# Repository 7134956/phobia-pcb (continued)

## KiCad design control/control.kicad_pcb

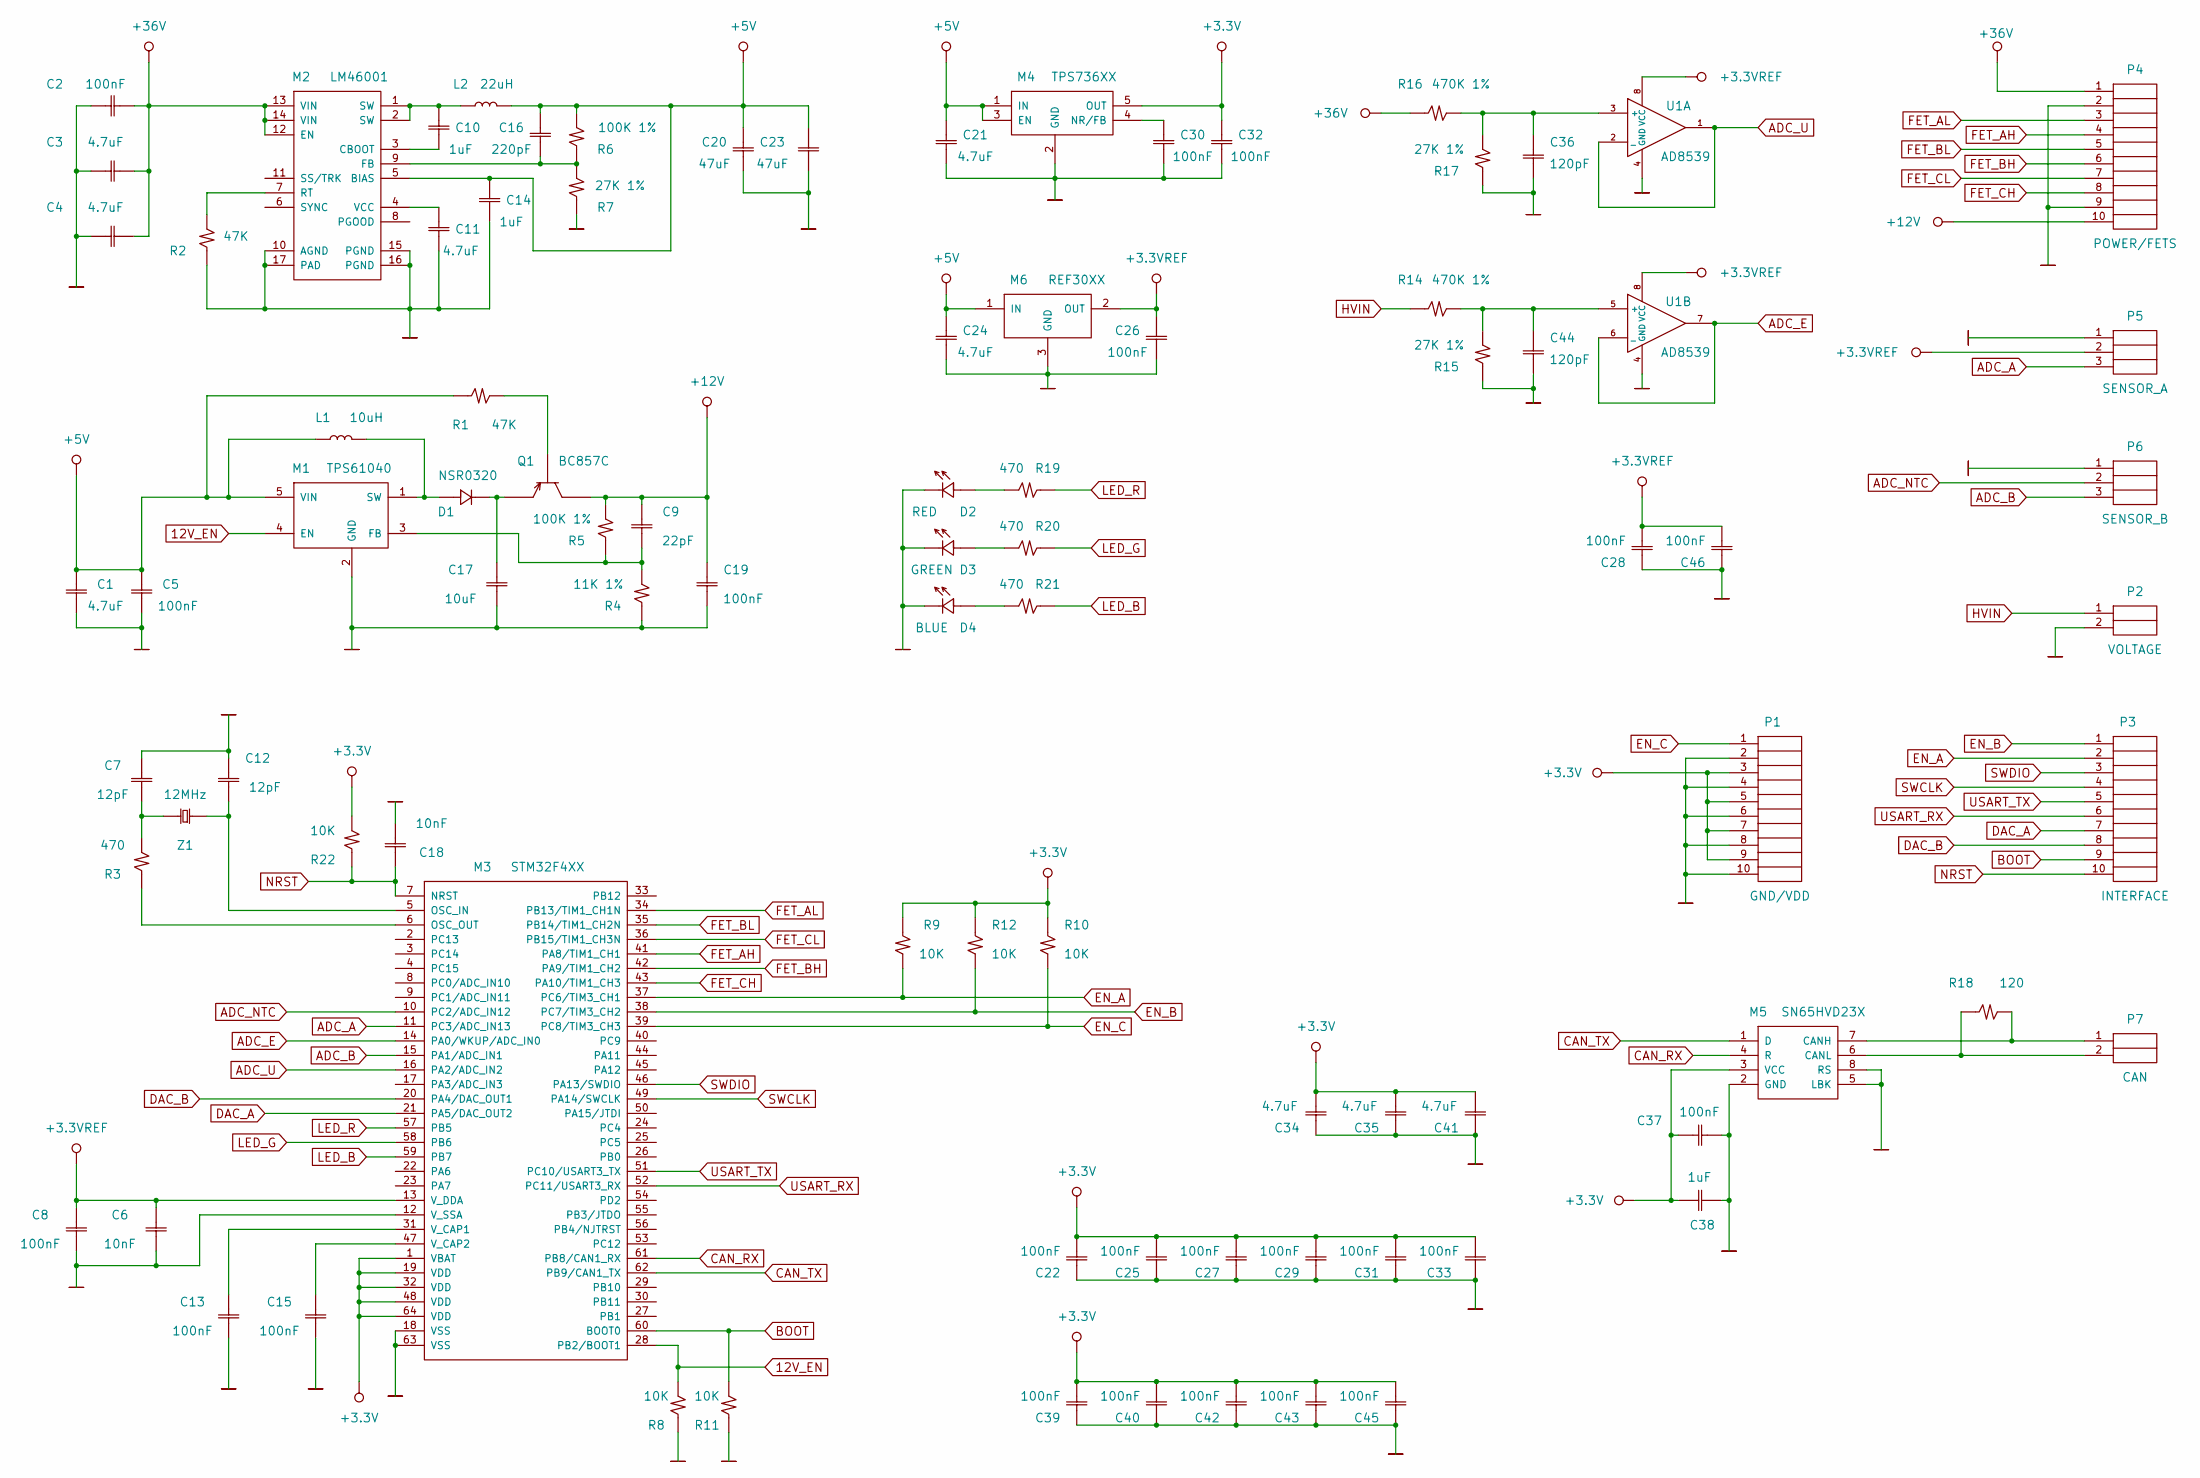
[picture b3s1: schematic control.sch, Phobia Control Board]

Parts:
C1, C11, C21, C24, C34, C35, C41: 4.7uF; SM0805
C2: 100nF; SM0805
C3, C4: 4.7uF; SM2220
C5, C8, C13, C15, C19, C22, C25, C26, C27, C28, C29, C30, C31, C32, C33, C37, C39, C40, C42, C43, C45, C46: 100nF; SM0603
C6, C18: 10nF; SM0603
C7, C12: 12pF; SM0603
C9: 22pF; SM0603
C10, C14, C38: 1uF; SM0805
C16: 220pF; SM0603
C17: 10uF; SM1210
C20, C23: 47uF; SM1210
C36, C44: 120pF; SM0603
D1: NSR0320; SOD-232
D2: RED; SM0603
D3: GREEN; SM0603
D4: BLUE; SM0603
L1: 10uH; COIL3
L2: 22uH; COIL8
M1: TPS61040; SOT23-5
M2: LM46001; HTSSOP16
M3: STM32F4XX; LQFP-64
M4: TPS736XX; SOT23-5
M5: SN65HVD23X; SO8
M6: REF30XX; SOT23
P1: GND/VDD; PLS10
P2: VOLTAGE; PLS2
P3: INTERFACE; PLS10
P4: POWER/FETS; PLS10
P5: SENSOR_A; PLS3
P6: SENSOR_B; PLS3
P7: CAN; PLS2
Q1: BC857C; SOT23
R1, R2: 47K; SM0603
R3, R19, R20, R21: 470; SM0603
R4: 11K 1%; SM0603
R5, R6: 100K 1%; SM0603
R7, R15, R17: 27K 1%; SM0603
R8, R9, R10, R11, R12, R22: 10K; SM0603
R14, R16: 470K 1%; SM0603
R18: 120; SM1206
U1: AD8539; MSOP8
Z1: 12MHz; SMD_Z3225

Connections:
12V_EN: M1.4 (EN), M3.28 (PB2/BOOT1), R8.2
+3.3V: C22.1, C25.1, C27.1, C29.1, C31.1, C32.1, C33.1, C34.1, C35.1, C37.2, C38.2, C39.1, C40.1, C41.1, C42.1, C43.1, C45.1, M3.1 (VBAT), M3.19 (VDD), M3.32 (VDD), M3.48 (VDD), M3.64 (VDD), M4.5 (OUT), M5.3 (VCC), P1.3, P1.5, P1.7, P1.9, R9.1, R10.1, R12.1, R22.2
+3.3VREF: C6.1, C8.1, C26.1, C28.1, C46.1, M3.13 (V_DDA), M6.2 (OUT), P5.2, U1.8 (VCC)
+5V: C1.1, C5.1, C14.1, C16.1, C20.1, C21.1, C23.1, C24.1, L1.1, L2.2, M1.5 (VIN), M2.5 (BIAS), M4.1 (IN), M4.3 (EN), M6.1 (IN), R1.1, R6.2
+12V: C9.1, C19.1, P4.10, Q1.2 (C), R5.2
+36V: C2.1, C3.1, C4.1, M2.12 (EN), M2.13 (VIN), M2.14 (VIN), P4.1, R16.1
ADC_A: M3.11 (PC3/ADC_IN13), P5.3
ADC_B: M3.15 (PA1/ADC_IN1), P6.3
ADC_E: M3.14 (PA0/WKUP/ADC_IN0), U1.6 (_), U1.7
ADC_NTC: M3.10 (PC2/ADC_IN12), P6.2
ADC_U: M3.16 (PA2/ADC_IN2), U1.1, U1.2 (_)
BOOT: M3.60 (BOOT0), P3.9, R11.2
CAN_RX: M3.61 (PB8/CAN1_RX), M5.4 (R)
CAN_TX: M3.62 (PB9/CAN1_TX), M5.1 (D)
DAC_A: M3.21 (PA5/DAC_OUT2), P3.7
DAC_B: M3.20 (PA4/DAC_OUT1), P3.8
EN_A: M3.37 (PC6/TIM3_CH1), P3.2, R9.2
EN_B: M3.38 (PC7/TIM3_CH2), P3.1, R12.2
EN_C: M3.39 (PC8/TIM3_CH3), P1.1, R10.2
FET_AH: M3.41 (PA8/TIM1_CH1), P4.4
FET_AL: M3.34 (PB13/TIM1_CH1N), P4.3
FET_BH: M3.42 (PA9/TIM1_CH2), P4.6
FET_BL: M3.35 (PB14/TIM1_CH2N), P4.5
FET_CH: M3.43 (PA10/TIM1_CH3), P4.8
FET_CL: M3.36 (PB15/TIM1_CH3N), P4.7
GND: C1.2, C2.2, C3.2, C4.2, C5.2, C6.2, C7.1, C8.2, C11.2, C12.1, C13.2, C14.2, C15.2, C17.2, C18.1, C19.2, C20.2, C21.2, C22.2, C23.2, C24.2, C25.2, C26.2, C27.2, C28.2, C29.2, C30.2, C31.2, C32.2, C33.2, C34.2, C35.2, C36.2, C37.1, C38.1, C39.2, C40.2, C41.2, C42.2, C43.2, C44.2, C45.2, C46.2, D2.1, D3.1, D4.1, M1.2 (GND), M2.10 (AGND), M2.15 (PGND), M2.16 (PGND), M2.17 (PAD), M3.12 (V_SSA), M3.18 (VSS), M3.63 (VSS), M4.2 (GND), M5.2 (GND), M5.5 (LBK), M5.8 (RS), M6.3 (GND), P1.2, P1.4, P1.6, P1.8, P1.10, P2.2, P4.2, P4.9, P5.1, P6.1, R2.1, R4.1, R7.1, R8.1, R11.1, R15.1, R17.1, U1.4 (GND)
HVIN: P2.1, R14.1
LED_B: M3.59 (PB7), R21.1
LED_G: M3.58 (PB6), R20.1
LED_R: M3.57 (PB5), R19.1
NRST: C18.2, M3.7 (NRST), P3.10, R22.1
unnamed: C7.2, R3.2, Z1.1
unnamed: C9.2, M1.3 (FB), R4.2, R5.1
unnamed: C10.1, L2.1, M2.1 (SW), M2.2 (SW)
unnamed: C10.2, M2.3 (CBOOT)
unnamed: C11.1, M2.4 (VCC)
unnamed: C12.2, M3.5 (OSC_IN), Z1.2
unnamed: C13.1, M3.31 (V_CAP1)
unnamed: C15.1, M3.47 (V_CAP2)
unnamed: C16.2, M2.9 (FB), R6.1, R7.2
unnamed: C17.1, D1.1, Q1.3 (E)
unnamed: C30.1, M4.4 (NR/FB)
unnamed: C36.1, R16.2, R17.2, U1.3 (+)
unnamed: C44.1, R14.2, R15.2, U1.5 (+)
unnamed: D1.2, L1.2, M1.1 (SW)
unnamed: D2.2, R19.2
unnamed: D3.2, R20.2
unnamed: D4.2, R21.2
unnamed: M2.7 (RT), R2.2
unnamed: M3.6 (OSC_OUT), R3.1
unnamed: M5.6 (CANL), P7.2, R18.1
unnamed: M5.7 (CANH), P7.1, R18.2
unnamed: Q1.1 (B), R1.2
SWCLK: M3.49 (PA14/SWCLK), P3.4
SWDIO: M3.46 (PA13/SWDIO), P3.3
USART_RX: M3.52 (PC11/USART3_RX), P3.6
USART_TX: M3.51 (PC10/USART3_TX), P3.5

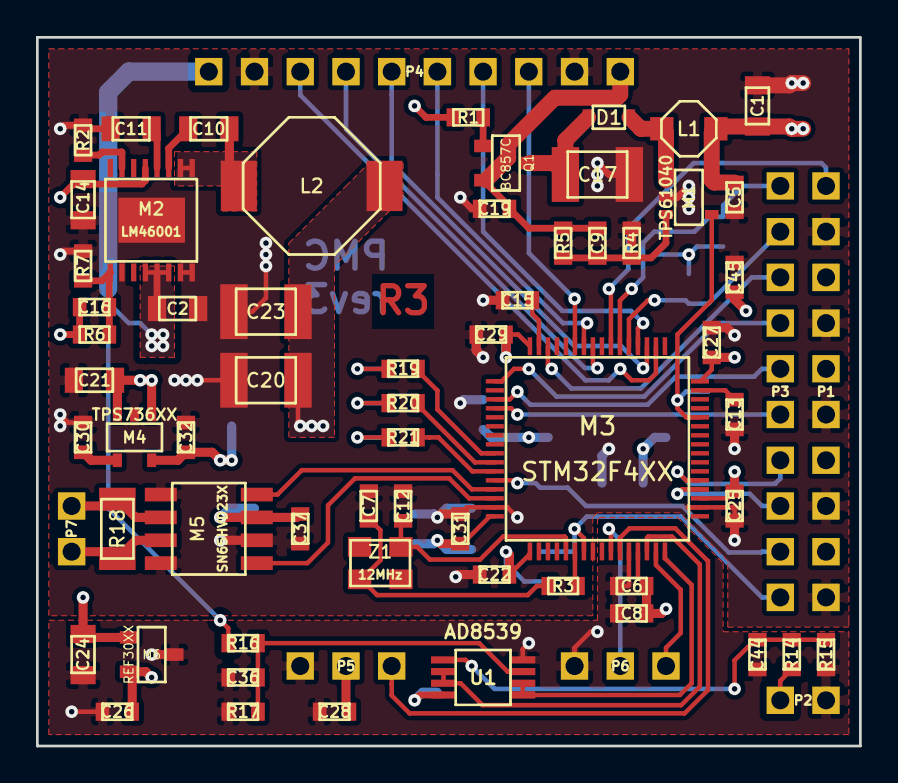
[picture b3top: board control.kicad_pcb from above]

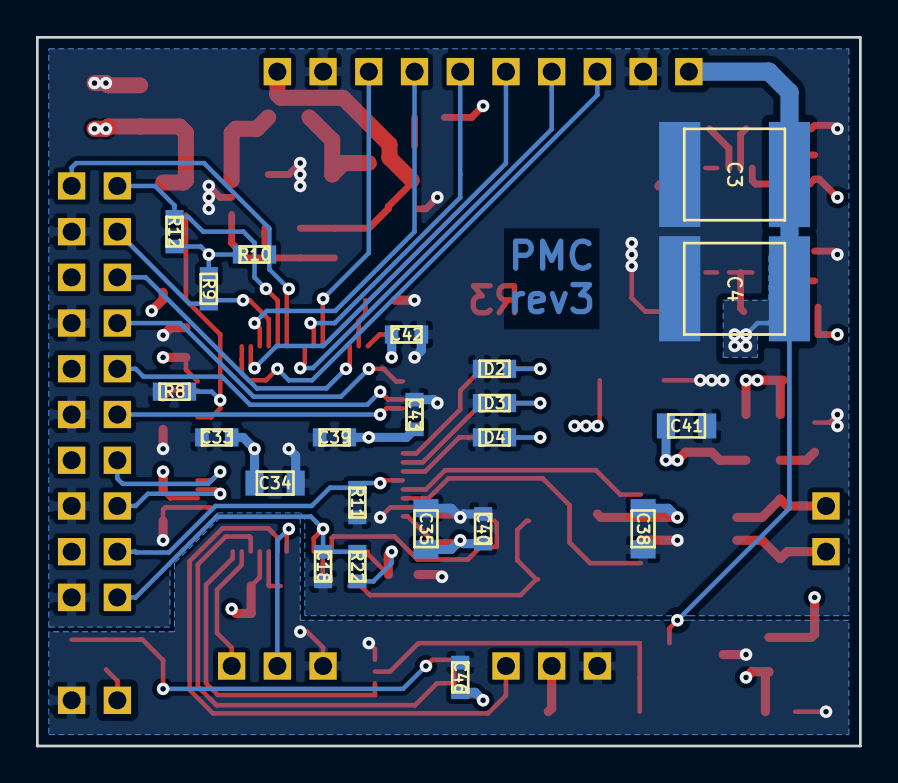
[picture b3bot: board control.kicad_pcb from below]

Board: 4 copper layers, 45.7 x 39.4 mm, 89 parts (22 on the bottom side), 57 nets.

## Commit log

2016-02-01 Initial commit with revision 1 draft.
2016-02-01 Added README.
2016-02-01 Fixed a mistake.
2016-02-02 Added tag rev1 for changeset 2688a04983ae
2016-02-02 Going to make a rev2.
2016-02-06 Small changes, enlarged supply rail clearance.
2016-02-09 Added OpAmp buffer, a lot of small fixes.
2016-02-15 Added encoder inputs on control board, removed SWD, changed USART.
2016-02-16 Added DAC outputs, SWD outputs, fixes.
2016-02-16 Added jumper outputs.
2016-03-25 Accumulated changes, large track width, encoder/hall interface, etc.
2016-03-30 Reduced decoupling capacitor bank like ESC, also added two row of pins, small fixes.
2016-03-31 Renew annotaion of power board, minor fixes.
2016-03-31 Added separate +5v polygon on control board.
2016-09-08 Fixed power pads mask clearance.
2016-09-19 Replaced ACS7XX sensors to the current shunt amplifiers.
2016-09-23 Small fixes for rev2.
2016-09-24 Added tag rev2 for changeset 79f38fd7bc1a
2016-10-30 Fixed a few small mistakes.
2017-05-09 Added revison 3.
2017-05-09 Added tag rev3 for changeset 9c580cb6d94c
2017-07-08 Fixed a little mistake.
2018-01-07 There is a single board design.
2018-04-01 Small fixes in schematic and pcb.
2018-04-06 Minor fixing.
2018-04-12 Fixed SilkS layers.
2018-04-14 Removed large cap outlines from SilkS layers.
2018-04-17 Fixed SilkS layers again.
2018-04-17 Fixed soldermask clearance.
2018-04-26 Added tag rev4a for changeset c6011a8fe1b5
2018-07-29 A new design with two 6-layer pcbs.
2018-08-25 Fixed routing of control pcb.
2018-08-28 Added tag rev4b for changeset 8665015f8bfb
2018-10-27 Added analog input and FAN output.
2018-11-09 Improved step-up layout.
2018-11-09 New annotation.
2019-01-19 Updated to rev4c.
2019-03-23 Moved CAN to 5v, fixed filter capacitors, etc.
2019-04-27 Added voltage bias resistors.
2019-06-02 New mosfet driver and current sensing amp.
2019-06-25 Two analog channels.
2019-08-01 Added mounting holes.
2019-08-11 Added heatsink drawing, CC attribution.
2019-08-12 Added tag rev4c for changeset cce9644f946d
